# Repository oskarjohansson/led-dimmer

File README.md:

# LED Dimmer
> Created by Oskar Johansson

**This project aims to fill the hole of nice LED dimmers for low voltage DC. **   

## Goals 
> The goals of this project:
```
- Create a LED dimmer for 12/24 V
- Able to completly turn on/off from only the potentiometer
- Handle ~100 W
```

## Directories 
```
LED Dimmer
├── document        # Generic document folder
│   ├── datasheet   # Datasheet for hardware components  
├── hardware        
│   ├── cad         # 3D models
│   │   └── stl     # 3D print files
│   ├── pcb         # Schematic, layout and production files
│   │   └── gerber  # Production files
│   │   └── library # Library for project       
└── img              # Firmware files
```

## Installation
> How to install the LED dimmer

## Usage
> How to use the LED dimmer

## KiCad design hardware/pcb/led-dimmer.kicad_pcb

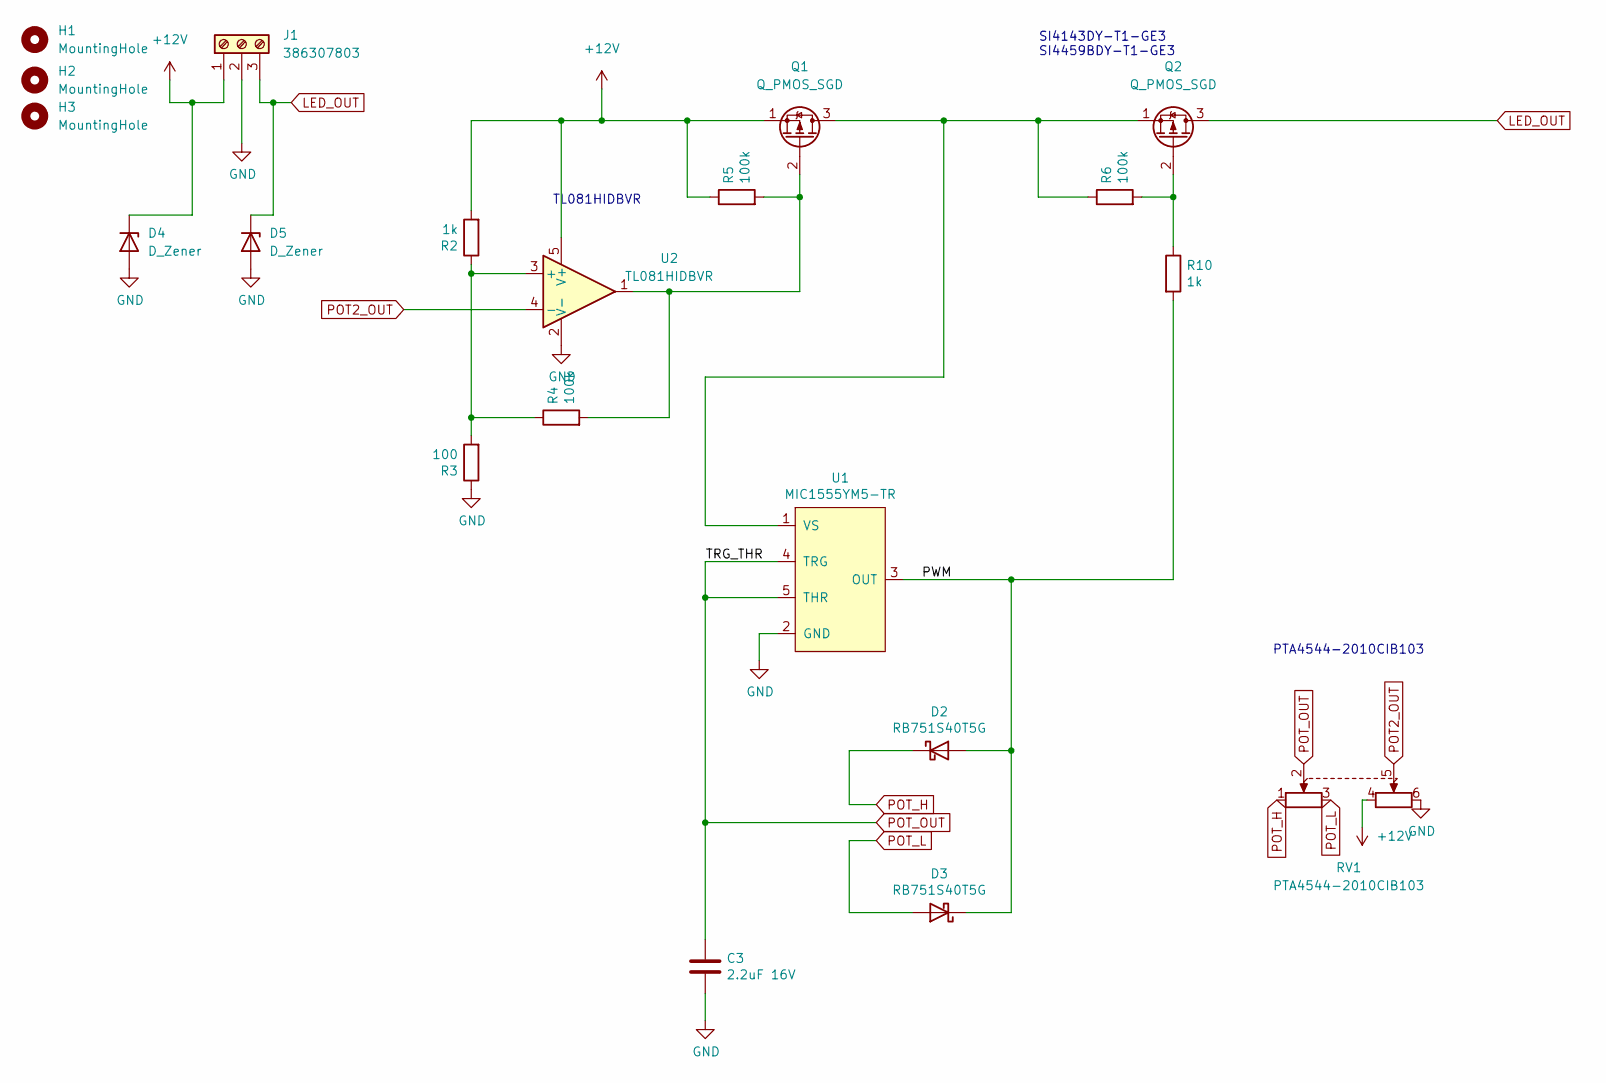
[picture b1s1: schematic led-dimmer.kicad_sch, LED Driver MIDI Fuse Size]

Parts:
C3: 2.2uF 16V; C_0603_1608Metric
D2, D3: RB751S40T5G; D_SOD-523; MPN RB751S40T5G
D4, D5: D_Zener; D_SOD-128
H1, H2, H3: MountingHole; MountingHole_3.2mm_M3_Pad_Via
J1: 386307803
Q1, Q2: Q_PMOS_SGD; SI4143DY-T1-GE3
R2, R10: 1k; R_0603_1608Metric
R3: 100; R_0603_1608Metric
R4, R5, R6: 100k; R_0603_1608Metric
RV1: PTA4544-2010CIB103
U1: MIC1555YM5-TR; SOT-23-5; MPN MIC1555YM5-TR
U2: TL081HIDBVR; SOT-23-5

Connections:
+12V: D4.1 (K), J1.1, Q1.1 (S), R2.2, R5.1, RV1.4, U2.5 (V+)
/PWM: D2.2 (A), D3.1 (K), R10.2, U1.3 (OUT)
GND: C3.2, D4.2 (A), D5.2 (A), J1.2, R3.1, RV1.6, U1.2 (GND), U2.2 (V-)
LED_OUT: D5.1 (K), J1.3, Q2.3 (D)
unnamed: R2.1, R3.2, R4.1, U2.3 (+)
unnamed: Q1.2 (G), R4.2, R5.2, U2.1
unnamed: Q1.3 (D), Q2.1 (S), R6.1, U1.1 (VS)
unnamed: Q2.2 (G), R6.2, R10.1
POT2_OUT: RV1.5, U2.4 (-)
POT_H: D2.1 (K), RV1.1
POT_L: D3.2 (A), RV1.3
POT_OUT: C3.1, RV1.2, U1.4 (TRG), U1.5 (THR)

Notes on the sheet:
TL081HIDBVR
PTA4544-2010CIB103
SI4143DY-T1-GE3 SI4459BDY-T1-GE3

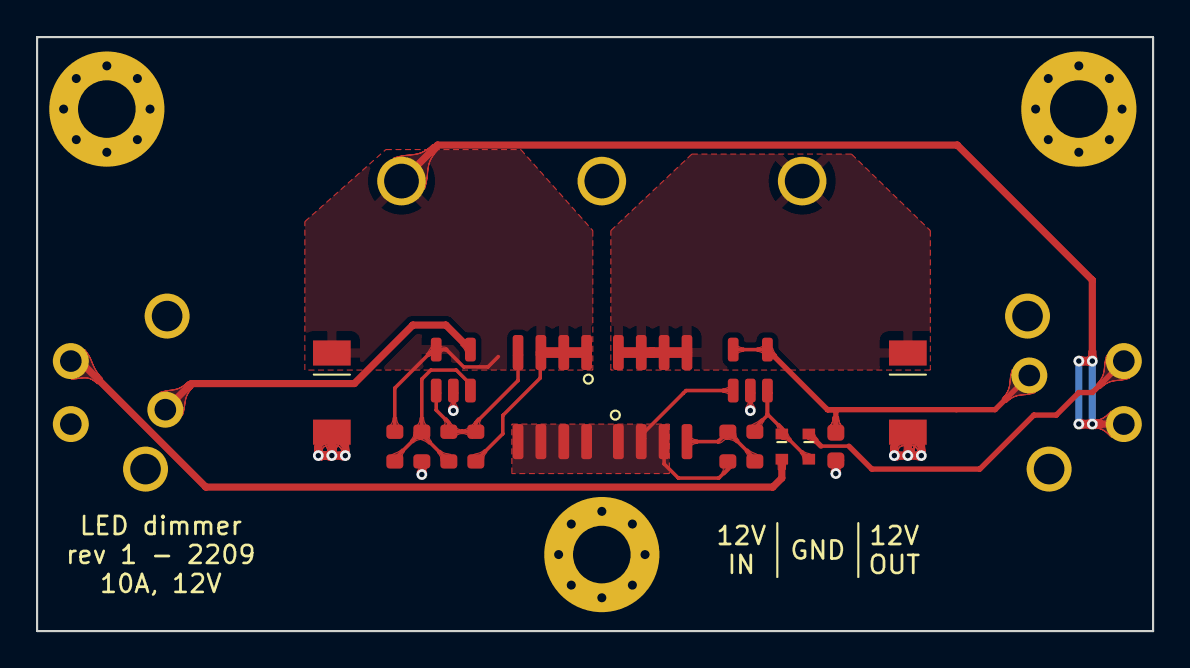
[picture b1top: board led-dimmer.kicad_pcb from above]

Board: 2 copper layers, 62.0 x 33.0 mm, 20 parts (1 on the bottom side), 12 nets.

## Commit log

2022-09-21 Add voltage trigger image
    Found on Arduino forum.
2022-09-21 First schematic with OP amp
2022-09-22 Schematic done
    Made some of the footprint and layout.
2022-09-23 First release
    A first release which is ordered from JLC.
